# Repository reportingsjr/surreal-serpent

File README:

This light ring is intended to go on the intake of a fume extractor I am designing.

The assembly can be done by JLC excluding the Molex Picoblade connector on the back.

The input is a 12V PWM signal. At 100% duty cycle the current draw is approximately 450mA, divided evenly(ish) across ten strings of LEDs.

This project is only half organized, because I spent more time than I wanted on the design and assembly steps and don't feel like spending more energy organizing a hobby project. :)

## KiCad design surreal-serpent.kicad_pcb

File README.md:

This light ring is intended to go on the intake of a fume extractor I am designing.

The assembly can be done by JLC excluding the Molex Picoblade connector on the back.

The input is a 12V PWM signal. At 100% duty cycle the current draw is approximately 450mA, divided evenly(ish) across ten strings of LEDs.

This project is only half organized, because I spent more time than I wanted on the design and assembly steps and don't feel like spending more energy organizing a hobby project. :)

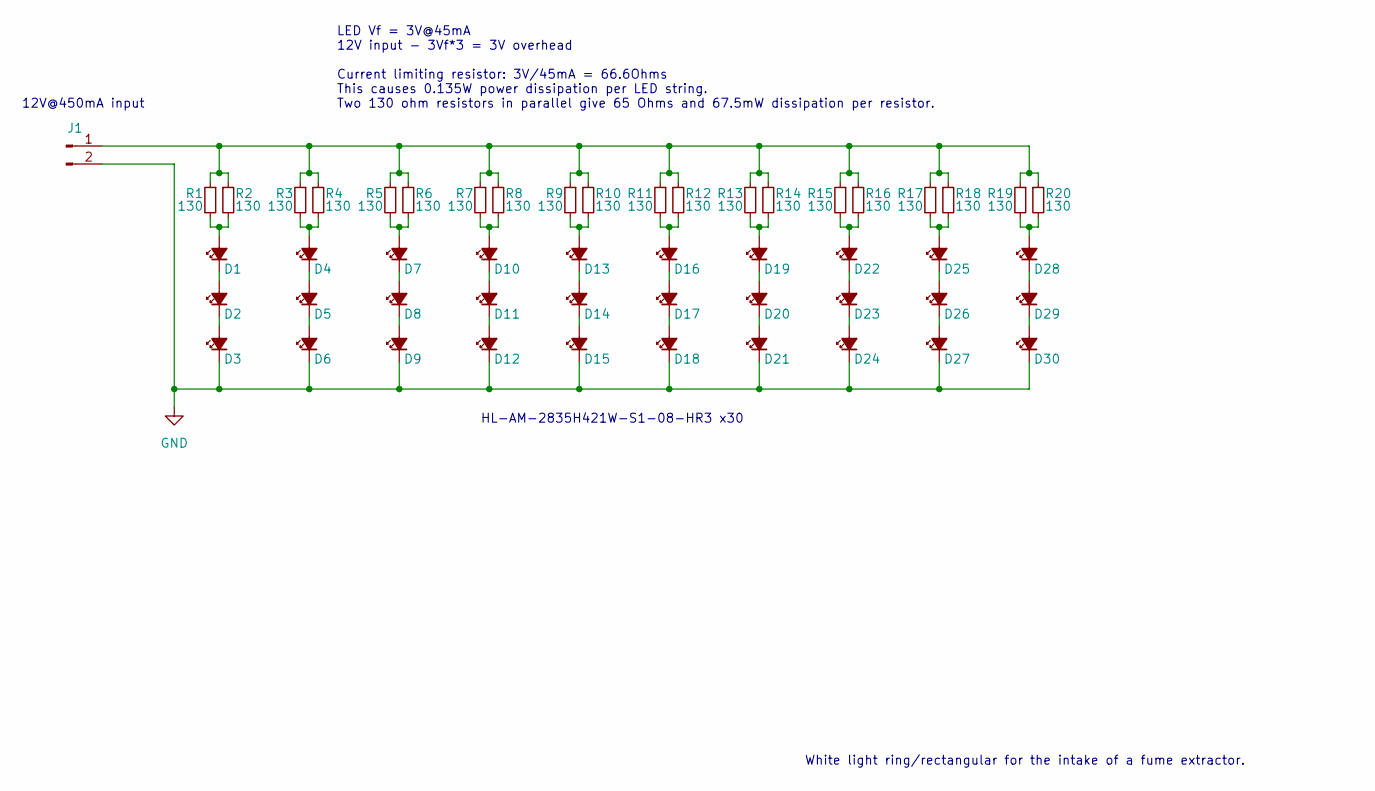
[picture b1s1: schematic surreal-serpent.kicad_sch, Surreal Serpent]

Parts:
D1, D2, D3, D4, D5, D6, D7, D8, D9, D10, D11, D12, D13, D14, D15, D16, D17, D18, D19, D20, D21, D22, D23, D24, D25, D26, D27, D28, D29, D30: HL-AM-2835H421W-S1-08-HR3; C210316; LCSC C210316
J1: Conn_01x02_Male; Molex_PicoBlade_53261-0271_1x02-1MP_P1.25mm_Horizontal; part number 0532610271
R1, R2, R3, R4, R5, R6, R7, R8, R9, R10, R11, R12, R13, R14, R15, R16, R17, R18, R19, R20: 130; R_0603_1608Metric; LCSC C22796

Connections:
GND: D3.1 (K), D6.1 (K), D9.1 (K), D12.1 (K), D15.1 (K), D18.1 (K), D21.1 (K), D24.1 (K), D27.1 (K), D30.1 (K), J1.2
unnamed: D1.1 (K), D2.2 (A)
unnamed: D1.2 (A), R1.2, R2.2
unnamed: D2.1 (K), D3.2 (A)
unnamed: D4.1 (K), D5.2 (A)
unnamed: D4.2 (A), R3.2, R4.2
unnamed: D5.1 (K), D6.2 (A)
unnamed: D7.1 (K), D8.2 (A)
unnamed: D7.2 (A), R5.2, R6.2
unnamed: D8.1 (K), D9.2 (A)
unnamed: D10.1 (K), D11.2 (A)
unnamed: D10.2 (A), R7.2, R8.2
unnamed: D11.1 (K), D12.2 (A)
unnamed: D13.1 (K), D14.2 (A)
unnamed: D13.2 (A), R9.2, R10.2
unnamed: D14.1 (K), D15.2 (A)
unnamed: D16.1 (K), D17.2 (A)
unnamed: D16.2 (A), R11.2, R12.2
unnamed: D17.1 (K), D18.2 (A)
unnamed: D19.1 (K), D20.2 (A)
unnamed: D19.2 (A), R13.2, R14.2
unnamed: D20.1 (K), D21.2 (A)
unnamed: D22.1 (K), D23.2 (A)
unnamed: D22.2 (A), R15.2, R16.2
unnamed: D23.1 (K), D24.2 (A)
unnamed: D25.1 (K), D26.2 (A)
unnamed: D25.2 (A), R17.2, R18.2
unnamed: D26.1 (K), D27.2 (A)
unnamed: D28.1 (K), D29.2 (A)
unnamed: D28.2 (A), R19.2, R20.2
unnamed: D29.1 (K), D30.2 (A)
unnamed: J1.1, R1.1, R2.1, R3.1, R4.1, R5.1, R6.1, R7.1, R8.1, R9.1, R10.1, R11.1, R12.1, R13.1, R14.1, R15.1, R16.1, R17.1, R18.1, R19.1, R20.1

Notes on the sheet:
12V@450mA input
LED Vf = 3V@45mA 12V input - 3Vf*3 = 3V overhead Current limiting resistor: 3V/45mA = 66.6Ohms This causes 0.135W power dissipation per LED string. Two 130 ohm resistors in parallel give 65 Ohms and 67.5mW dissipation per resistor.
HL-AM-2835H421W-S1-08-HR3 x30
White light ring/rectangular for the intake of a fume extractor.

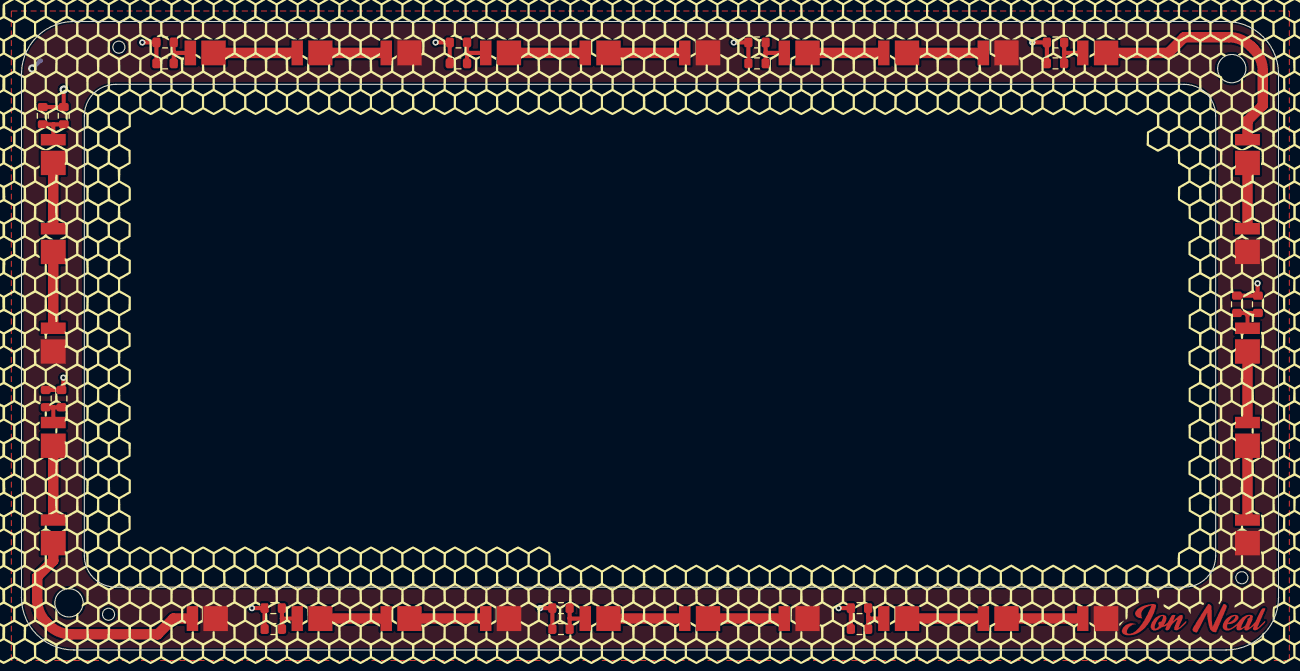
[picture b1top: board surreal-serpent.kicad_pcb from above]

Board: 2 copper layers, 120.0 x 60.0 mm, 51 parts (1 on the bottom side), 32 nets.

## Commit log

2021-09-23 Initial release of design, untested, but ordered.
2021-09-23 Add board render image
2021-09-23 Update and rename README to README.md
    Also added PCB render.
